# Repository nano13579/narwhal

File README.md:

# narwhal

A macropad with 9 keys, 1 EC11 Rotary Encoder, 9 through-hole 1N4148 Diodes, and 1 SK6812 MINI.

## PCB

Used KiCad for setting up the schematic and pcb.
Utilized a matrix setup for the switches and used diodes for backlight. 
I found that enjoyed routing traces and adding narwhals to the silkscreen.
I did run into a few issues with spacing on the pcb and had to redo the traces once or twice. 

## CAD

Used Fusion for the CAD. 
I had a little problem with fitting the encoder into the case. Eventually left a little bit of space so
pcb can be seen underneath, both near the rotary encoder and next to the XIAO and neopixel.
The narwhals on the silkscreen can be seen through the space on the case. 

## Firmware

Used kmk for firmware. Rotary encoder increases/decreases the volume. Currently have a basic setup for key mapping but will likely change them to macros later.

## BOM

1 x Seeed XIAO RP2040

9 x 1N4148 Diodes

9 x MX-Style switches

1 x EC11 Rotary encoder

9 x Blank DSA keycaps

1 x SK6812 MINI-E LED

If possible a black case

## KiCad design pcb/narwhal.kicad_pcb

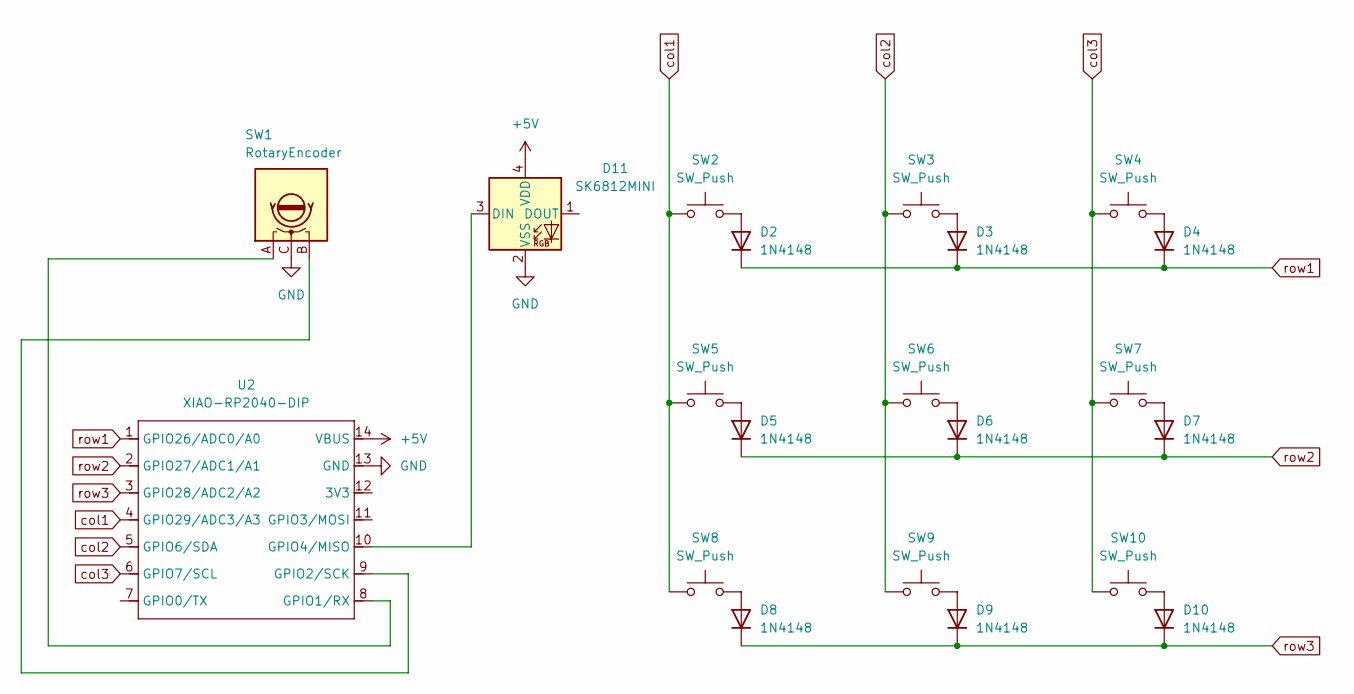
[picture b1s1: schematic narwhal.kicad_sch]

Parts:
D2, D3, D4, D5, D6, D7, D8, D9, D10: 1N4148; D_DO-35_SOD27_P7.62mm_Horizontal
D11: SK6812MINI; LED_SK6812MINI_PLCC4_3.5x3.5mm_P1.75mm
SW1: RotaryEncoder; RotaryEncoder_Alps_EC11E-Switch_Vertical_H20mm
SW2, SW3, SW4, SW5, SW6, SW7, SW8, SW9, SW10: SW_Push; SW_Cherry_MX_1.00u_PCB
U2: XIAO-RP2040-DIP

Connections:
+5V: D11.4 (VDD), U2.14 (VBUS)
GND: D11.2 (VSS), SW1.C, U2.13 (GND)
unnamed: D2.2 (A), SW2.2
unnamed: D3.2 (A), SW3.2
unnamed: D4.2 (A), SW4.2
unnamed: D5.2 (A), SW5.2
unnamed: D6.2 (A), SW6.2
unnamed: D7.2 (A), SW7.2
unnamed: D8.2 (A), SW8.2
unnamed: D9.2 (A), SW9.2
unnamed: D10.2 (A), SW10.2
unnamed: D11.3 (DIN), U2.10 (GPIO4/MISO)
unnamed: SW1.A, U2.8 (GPIO1/RX)
unnamed: SW1.B, U2.9 (GPIO2/SCK)
col1: SW2.1, SW5.1, SW8.1, U2.4 (GPIO29/ADC3/A3)
col2: SW3.1, SW6.1, SW9.1, U2.5 (GPIO6/SDA)
col3: SW4.1, SW7.1, SW10.1, U2.6 (GPIO7/SCL)
row1: D2.1 (K), D3.1 (K), D4.1 (K), U2.1 (GPIO26/ADC0/A0)
row2: D5.1 (K), D6.1 (K), D7.1 (K), U2.2 (GPIO27/ADC1/A1)
row3: D8.1 (K), D9.1 (K), D10.1 (K), U2.3 (GPIO28/ADC2/A2)

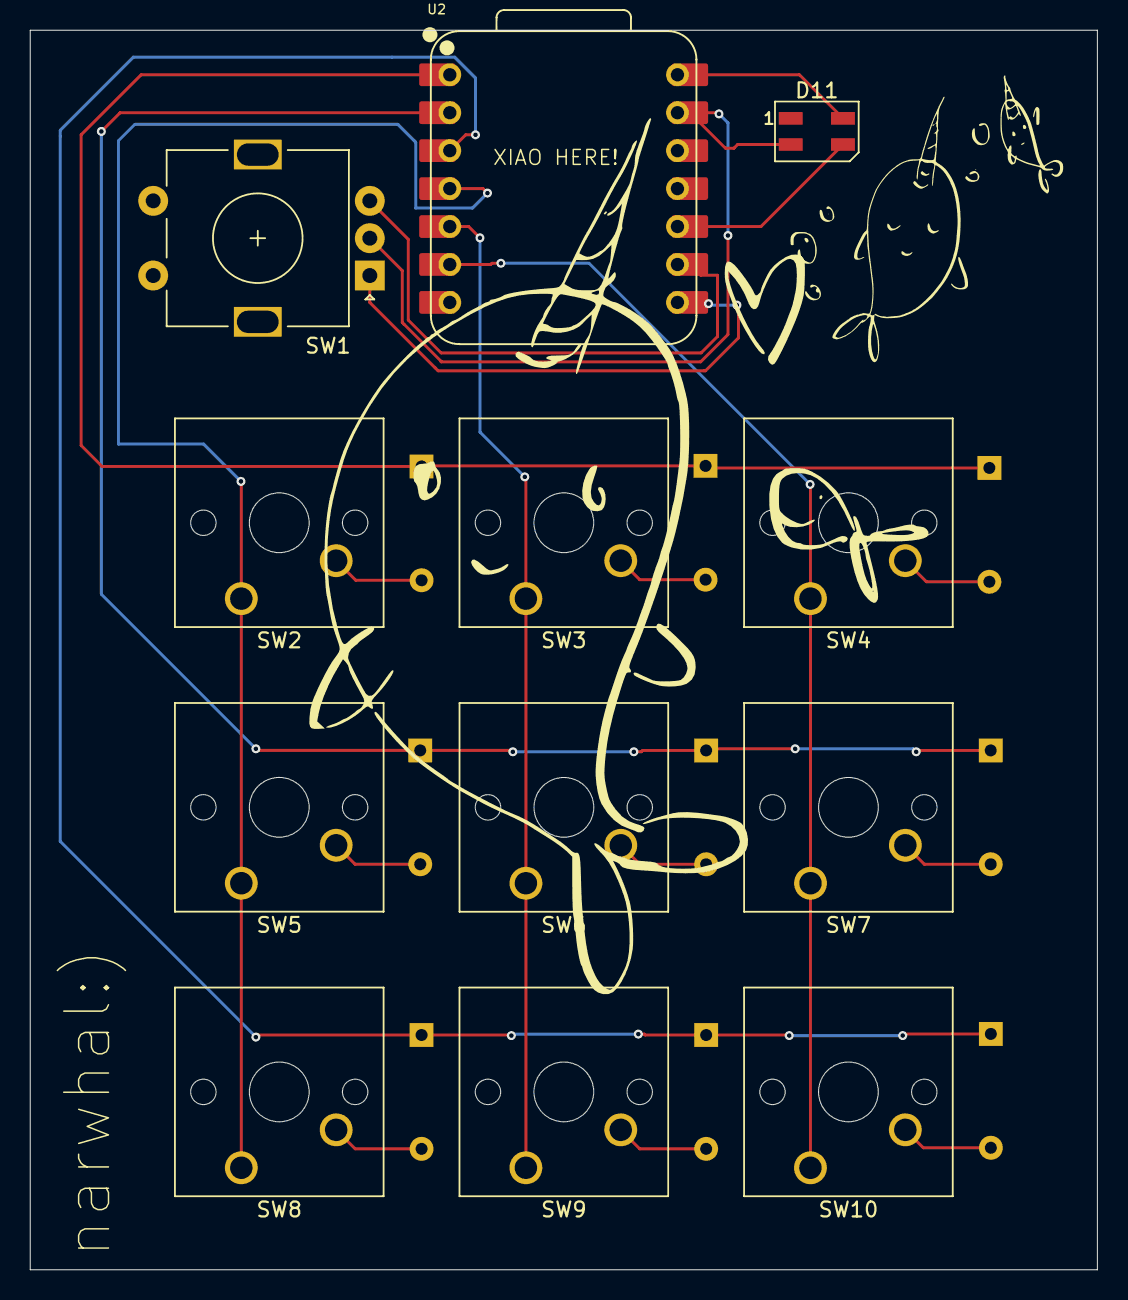
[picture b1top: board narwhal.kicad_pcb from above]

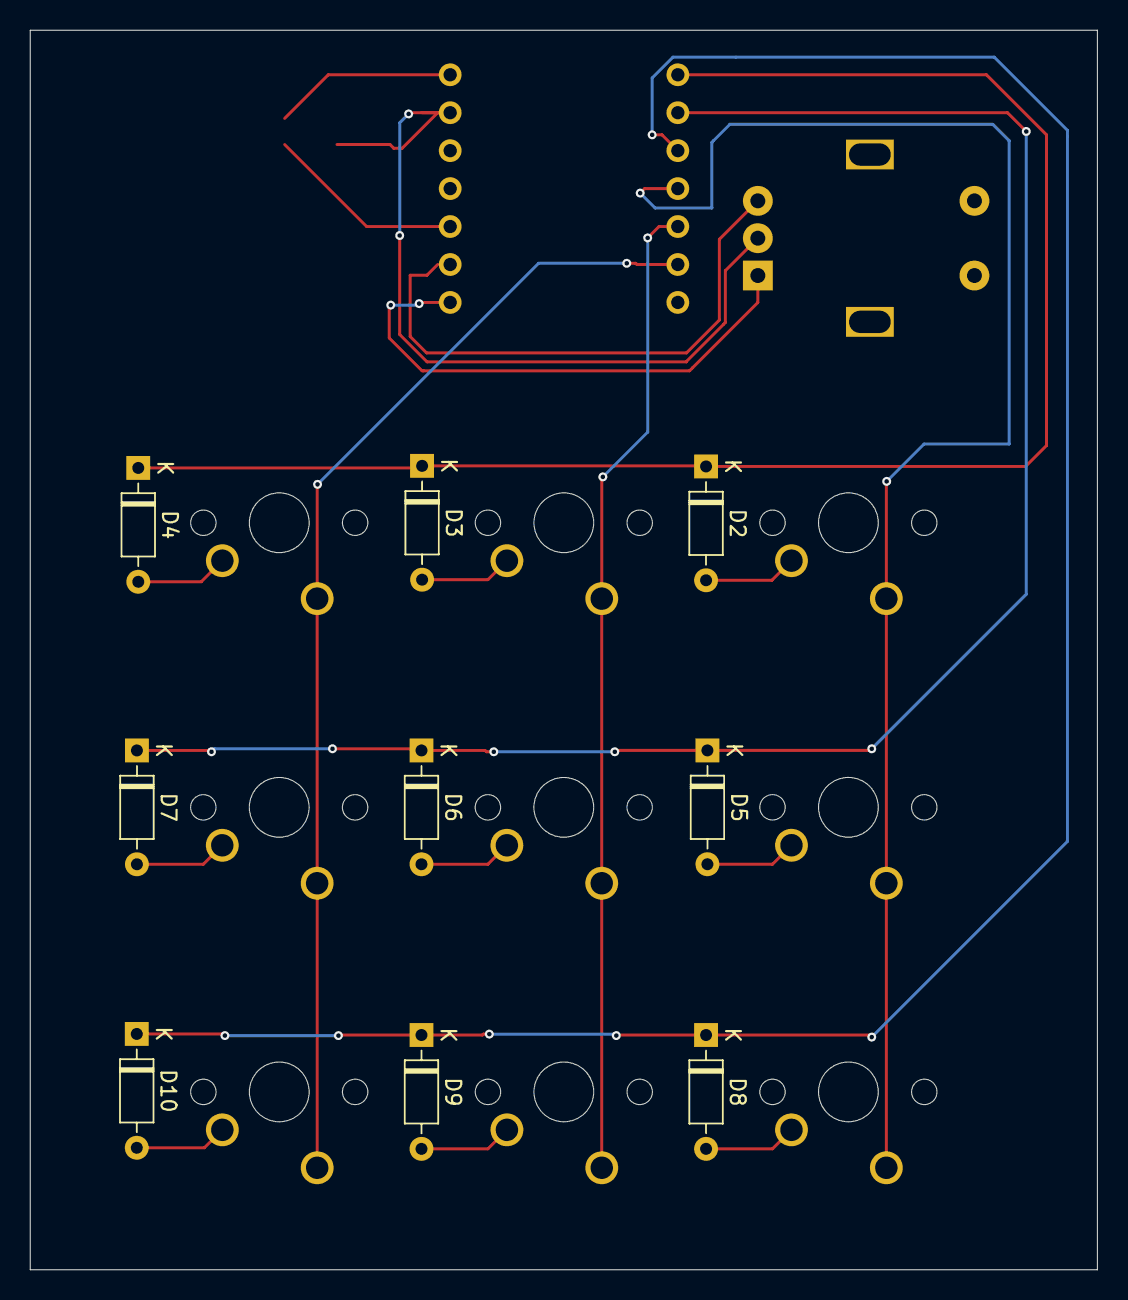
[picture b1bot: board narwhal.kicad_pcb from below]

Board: 2 copper layers, 71.4 x 83.0 mm, 21 parts (9 on the bottom side), 20 nets.

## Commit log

2025-05-24 finished
2025-05-24 renamed main.py
2025-05-24 changes to README.md
